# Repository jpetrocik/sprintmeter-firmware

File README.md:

# sprintmeter-firmware
A BMX sprint timer for logging sprint times both on and off the track.

Sprint data is sent via bluetooth to Android devices.  Leveleraging the display and storage capacity of Android 
smartphone and tablets to display and log spring data.  Unlike normal bike computers that display only current speed,
max speed, and distance sprintmeter logs data at 3-4 times a revolution.  SprintMeter shows speed, distance, and time
at 16" intervals.

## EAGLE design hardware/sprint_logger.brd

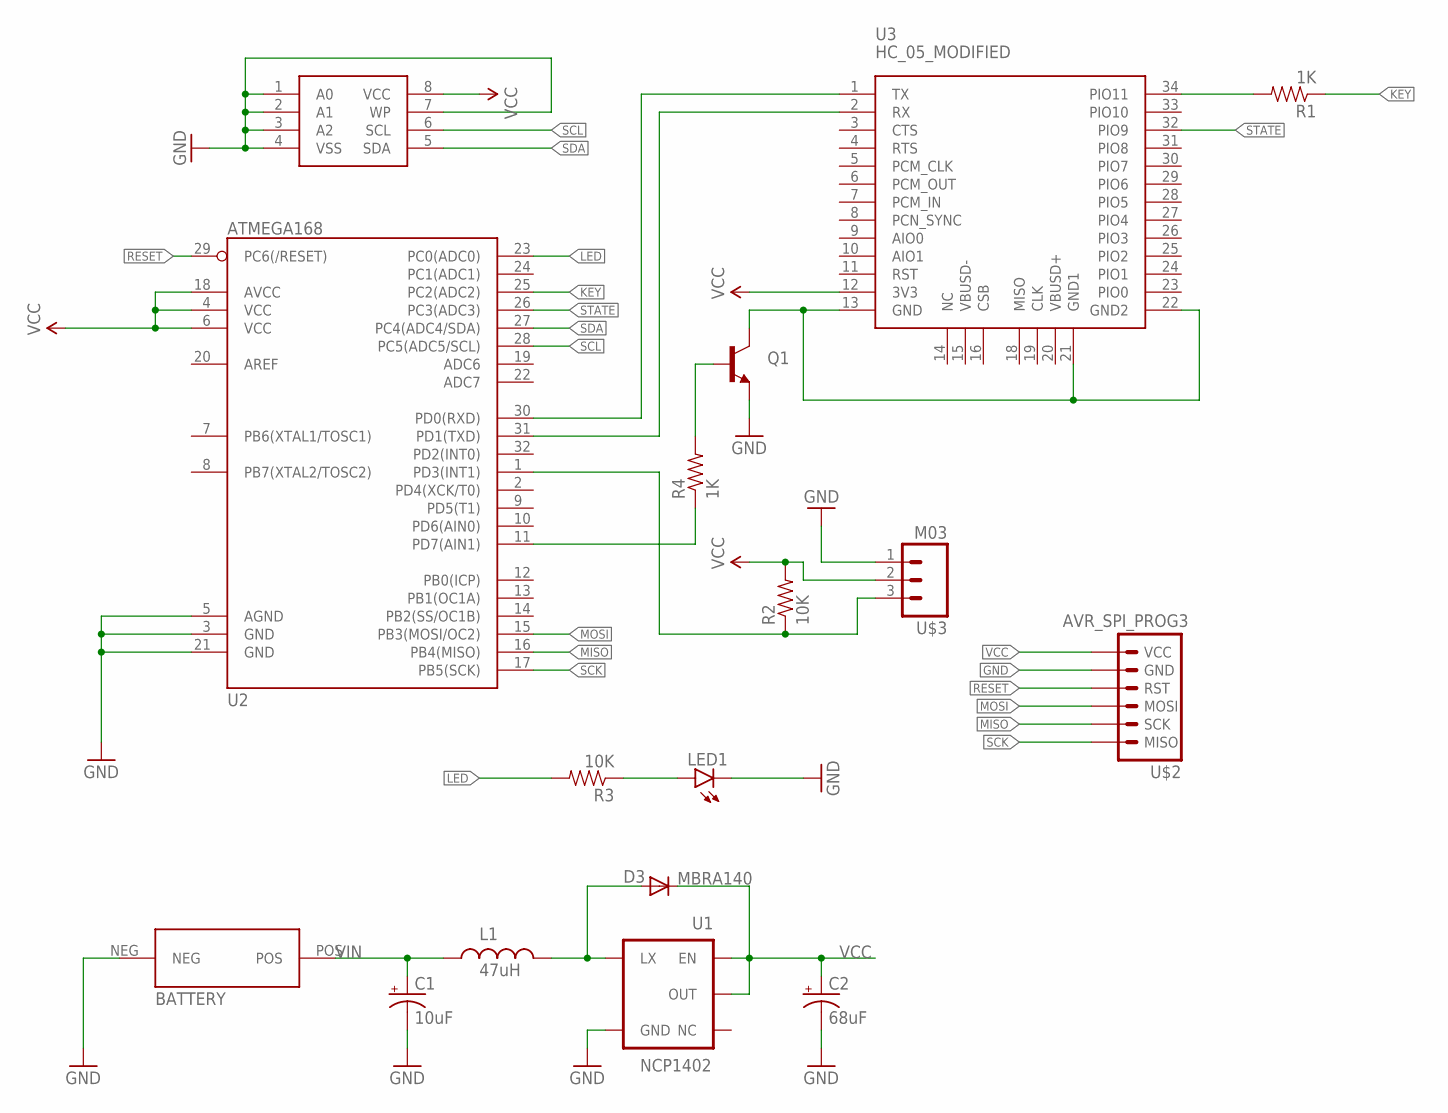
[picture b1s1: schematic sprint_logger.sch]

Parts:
BATTERY: BATHOLDER-N-2470
C1: 10uF; EIA3216
C2: 68uF; EIA3528
D3: MBRA140; SMA-DIODE
L1: 47uH; CR54
LED1: LED1206; LED-1206
Q1: TRANSISTOR_NPNSOT23; SOT23
R1, R4: 1K; 0805
R2, R3: 10K; 0805
U1: NCP1402; SOT23-5
U2: ATMEGA168; TQFP32-08
U3: HC_05_MODIFIED; BLUETOOTH_SMD_MODIFIED
U$1: 24AAXXX; SOIC-8-EIAJ
U$2: AVR_SPI_PROG3; 1X06-SMD_EDGE
U$3: M03; 1X06-SMD_EDGE

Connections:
GND: BATTERY.NEG, C1.C (-), C2.C (-), LED1.C, Q1.2 (E), U1.4 (GND), U2.3 (GND), U2.5 (AGND), U2.21 (GND), U$1.1 (A0), U$1.2 (A1), U$1.3 (A2), U$1.4 (VSS), U$1.7 (WP), U$2.2 (GND), U$3.1
KEY: R1.1, U2.25 (PC2(ADC2))
LED: R3.2, U2.23 (PC0(ADC0))
MISO: U2.16 (PB4(MISO)), U$2.5 (SCK)
MOSI: U2.15 (PB3(MOSI/OC2)), U$2.4 (MOSI)
unnamed: R2.1, U2.1 (PD3(INT1)), U$3.3
unnamed: D3.A, L1.P$2 (2), U1.5 (LX)
unnamed: U2.30 (PD0(RXD)), U3.1 (TX)
unnamed: U2.31 (PD1(TXD)), U3.2 (RX)
unnamed: Q1.3 (C), U3.13 (GND), U3.21 (GND1), U3.22 (GND2)
unnamed: LED1.A, R3.1
unnamed: Q1.1 (B), R4.2
unnamed: R4.1, U2.11 (PD7(AIN1))
unnamed: R1.2, U3.34 (PIO11)
RESET: U2.29 (PC6(/RESET)), U$2.3 (RST)
SCK: U2.17 (PB5(SCK)), U$2.6 (MISO)
SCL: U2.28 (PC5(ADC5/SCL)), U$1.6 (SCL)
SDA: U2.27 (PC4(ADC4/SDA)), U$1.5 (SDA)
STATE: U2.26 (PC3(ADC3)), U3.32 (PIO9)
VCC: C2.A (+), D3.C, R2.2, U1.1 (EN), U1.2 (OUT), U2.4 (VCC), U2.6 (VCC), U2.18 (AVCC), U3.12 (3V3), U$1.8 (VCC), U$2.1 (VCC), U$3.2
VIN: BATTERY.POS, C1.A (+), L1.P$1 (1)

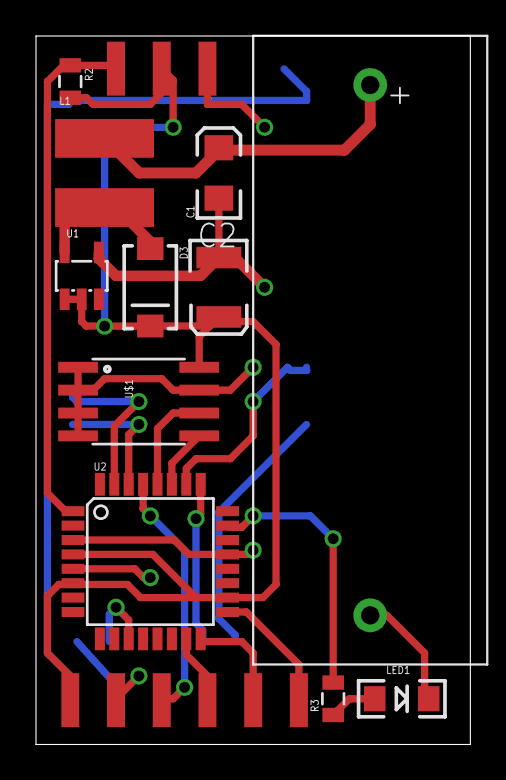
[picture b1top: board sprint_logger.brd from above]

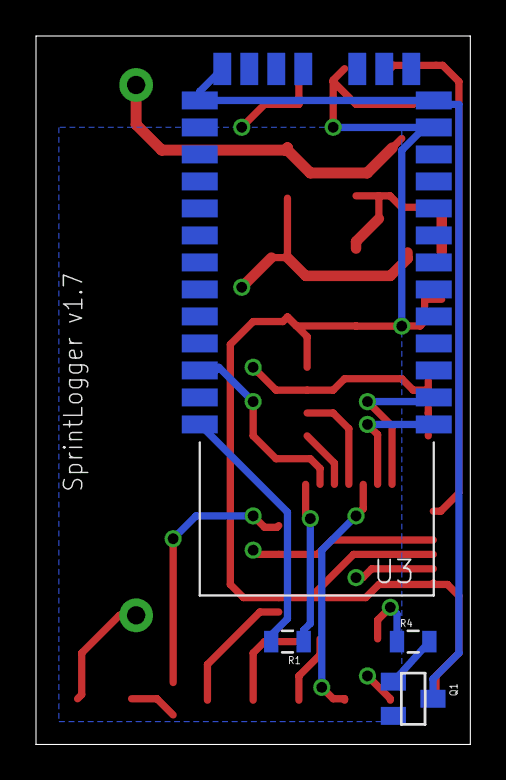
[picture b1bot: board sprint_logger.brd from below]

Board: 2 copper layers, 24.1 x 39.4 mm, 17 parts (4 on the bottom side), 21 nets.

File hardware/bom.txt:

Part    Value            Device               Package                Description                                                                                                                 
BATTERY BATHOLDER-N-2470 BATHOLDER-N-2470     BATHOLDER-N-2470       Digi-Key Part Number                                                                                              KEY1123-ND
C1      10uF             CAP_POL1206          EIA3216                Capacitor Polarized                                                                                                         
C2      68uF             CAP_POL3528          EIA3528                Capacitor Polarized                                                                                                         
D3      MBRA140          DIODESMA             SMA-DIODE              Diode                                                                                                                       
L1      47uH             INDUCTORCR54         CR54                   Inductors                                                                                                                   
Q1                       TRANSISTOR_NPNSOT23  SOT23                  Generic NPN BJT. MMBT2222 is the common NPN we use. 
R4      1K               RESISTOR0805-RES     0805                   Resistor                                                                                                                    
REED    M02              M02                  1X02-SMD_EDGE          Standard 2-pin 0.1" header. Use with                                                                                        
U$1     24AAXXX          24AAXXX              SOIC-8-EIAJ                                                                                                                                        
U$2     AVR_SPI_PROG3    AVR_SPI_PROG3        1X06-SMD_EDGE          SMD edge programer                                                                                                          
U1      NCP1402          V_REG_NCP1400SOT23-5 SOT23-5                Switching step-up voltage regulator                                                                                         
U2      ATMEGA168        ATMEGA168            TQFP32-08              Atmel 32-pin 8-bit micro, 16k flash.

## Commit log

2015-10-12 Migrated to github
2015-10-12 Adding schematics
2019-08-25 Moved firmware into firmware directory
2019-12-07 Intial v1.6 commit
2019-12-11 Converted to microseconds
2019-12-11 Adding android app
2019-12-12 Dropped speed, added diff
2019-12-12 Cleaned up sprint manager
2019-12-12 Added autoReady to TrackPractice
2019-12-12 Added sprint detection
2019-12-18 sleep revamped, sprint activity cleaned up, auto detected track sprints
2019-12-21 Added sleep, best times, checksum
2019-12-21 Adding speed smoothing
2019-12-21 Added best time/speed to sprint activity
2019-12-24 Added swipe navigation to sprint activity to view old sprints
2019-12-27 Cleaned up sprint swipe and fixed best displays
2019-12-27 Displays avg speed
2019-12-27 Fixed first split calcuation
2019-12-28 Moved ui updates when sprint ends to loadSprint
2019-12-28 Extracted loadSprint to AbstractSprintActivity
2019-12-28 reduce session window to 6 hours
2019-12-28 Reduced sleep time to 3 minutes
2019-12-29 .gitignore fix
2020-01-06 Alpha1 commit
2020-01-06 Removed unused BOUNCE constant
2020-01-07 TrackPractice updated

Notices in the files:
parts and their libraries:
SparkFun-DigitalIC: Licensing: CC v3.0 Share-Alike You are welcome to use this library for commercial purposes.
SparkFun-LED: Licensing: Creative Commons ShareAlike 4.0 International - https://creativecommons.org/licenses/by-sa/4.0
